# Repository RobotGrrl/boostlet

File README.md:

# Boostlet!

Embeddable circuit board to boost battery input to 5V intended for small robots. Useful access is provided to two logic level convertors for Neopixels, and a 3.3V regulator. Input and output are protected with PTCs, with the option to not populate with a solder jumper. Castellated connectors enable this circuit board to be added either surface mount or with through-hole 0.1" headers. 

---

## Documentation

[Boost IC: PAM2401](https://www.diodes.com/assets/Datasheets/PAM2401.pdf)

Dimensions: 35 mm x 40 mm

- V_IN: 0.9 - 4.75V
- V_OUT: 5V, 3A
- V_REG: 3.3V, 1A

### Connectors

J1
- VCC
- NEO_IN2
- NEO_OUT2
- BATT_SIG
- NEO_IN1
- NEO-OUT1
- GND

J2 (Input)
- V_IN (V_BATT)
- GND
- VCC

J3 (Output)
- V_OUT (5V)
- GND
- V_REG (3.3V)

### Solder Jumpers
- JP1: Bypass input PTC
- JP2: Enable 3.3V reg powered from 5V boost output
- JP3: Bypass output PTC
- JP4: Connect 3.3V reg output to Vcc _(be sure Vcc isn't connected to anything!)_

_Solder jumpers are open by default, add solder to connect the pads to close them_

Documentation provided under [CC-BY-4.0](https://creativecommons.org/licenses/by/4.0/)

---

## License

Boostlet! (C) Copyright Erin RobotZwrrl, Robot Missions Inc.

12-30-23 v1.0

[RobotZwrrl.xyz/boostlet](http://RobotZwrrl.xyz/boostlet)

[RobotMissions.org](https://RobotMissions.org)

This hardware is released under:

CERN Open Hardware License Version 2.0 - Permissive (CERN-OHL-P)

[https://cern-ohl.web.cern.ch/](https://cern-ohl.web.cern.ch/)

Disclaimer: Distributed as is. No warranty is given. Not responsible or liable for any damage or harm that result from this product.

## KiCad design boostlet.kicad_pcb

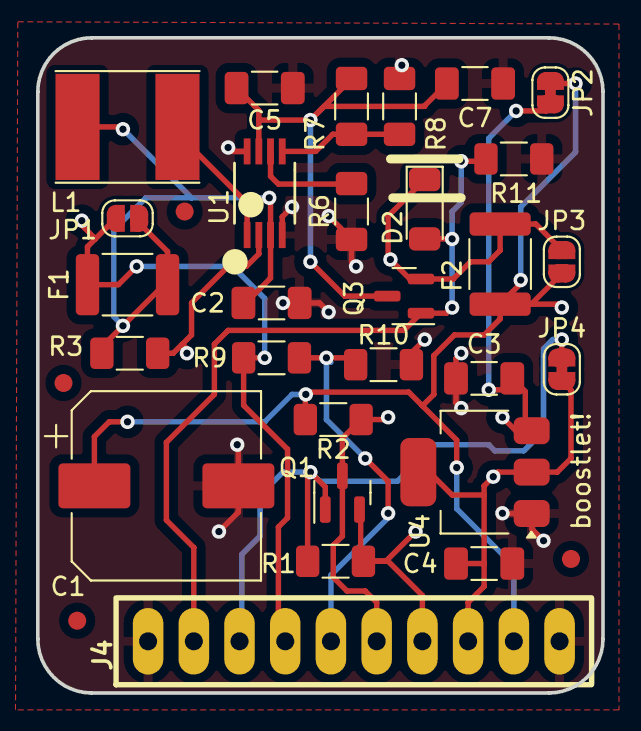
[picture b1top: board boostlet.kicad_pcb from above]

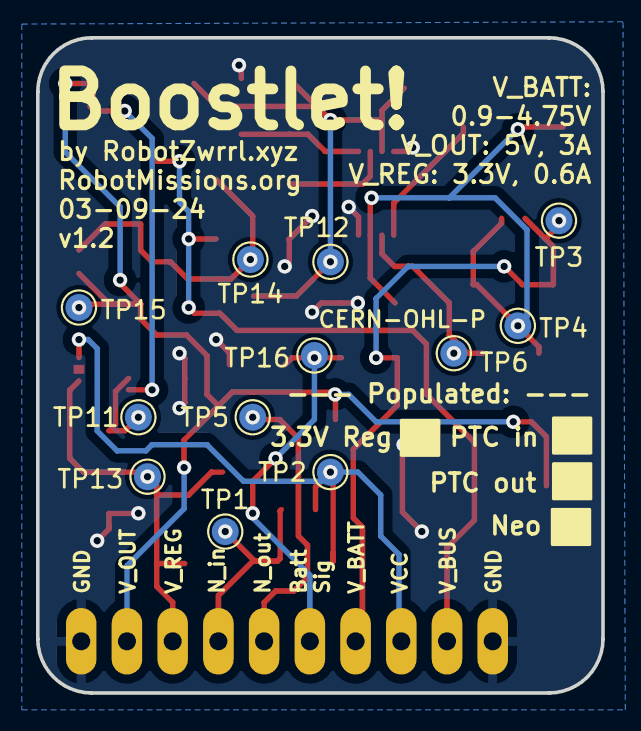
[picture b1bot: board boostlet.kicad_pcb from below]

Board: 2 copper layers, 31.4 x 36.4 mm, 44 parts (12 on the bottom side), 17 nets.

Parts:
C1: 1000 uF @ 16 V; CP_Elec_10x10
C2: 10 uF; C_1206_3216Metric_Pad1.33x1.80mm_HandSolder
C3, C4, C7: 1 uF; C_1206_3216Metric_Pad1.33x1.80mm_HandSolder
C5: 22 uF; C_1206_3216Metric_Pad1.33x1.80mm_HandSolder
D2: PMEG40T30ERX 40V 3A; D_SOD-123
F1: Polyfuse 6V, 1.5A I_h, 3A I_t, 500 ms; Fuse_1812_4532Metric_Pad1.30x3.40mm_HandSolder
F2: Polyfuse 16V, 1.25A I_h, 2.5A I_t, 400 ms; Fuse_1812_4532Metric_Pad1.30x3.40mm_HandSolder
FID1, FID2, FID3, FID4: Fiducial; Fiducial_1mm_Mask2mm
J4: Conn_01x10_Socket; Oval_1x10_P2.54mm
JP1, JP3: SolderJumper_2_Open; SolderJumper-2_P1.3mm_Open_RoundedPad1.0x1.5mm
JP2, JP4: SolderJumper_2_Bridged; SolderJumper-2_P1.3mm_Bridged_RoundedPad1.0x1.5mm
L1: 4.7 uH, 3 A; L_Taiyo-Yuden_NR-60xx_HandSoldering
Q1: BSS138; SOT-23
Q3: DMG3415U; SOT-23
R1, R2: 10k; R_1206_3216Metric_Pad1.30x1.75mm_HandSolder
R3, R6, R8, R11: 100k; R_1206_3216Metric_Pad1.30x1.75mm_HandSolder
R7: 750k; R_1206_3216Metric_Pad1.30x1.75mm_HandSolder
R9: 100; R_1206_3216Metric_Pad1.30x1.75mm_HandSolder
R10: 6.8k; R_1206_3216Metric_Pad1.30x1.75mm_HandSolder
TP1, TP2, TP3, TP4, TP5, TP6, TP11, TP12, TP13, TP14, TP15, TP16: TestPoint; TestPoint_Pad_D1.5mm
U1: PAM2401
U4: AP2111H-3.3TRG1; SOT-223-3_TabPin2

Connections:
/3.3V: C4.1, J4.8, JP4.1 (A), TP13.1, U4.2 (VO)
/5V: C1.1, F2.1, J4.9, JP2.1 (A), JP3.2 (B), R2.1, TP15.1
/BATT_SIG: J4.5, R9.2, R10.1, TP16.1
/NEO_IN1: J4.7, Q1.2 (S), R1.2, TP1.1
/NEO_OUT1: J4.6, Q1.3 (D), R2.2, TP5.1
/V_BATT: F1.2, J4.4, JP1.1 (A), R9.1, TP3.1
/V_BOOST: C5.1, C7.1, Q3.3 (D), R7.1, TP12.1, U1.7 (OUT)
/V_BUS: D2.2 (A), J4.2, Q3.1 (G), R11.1
GND: C1.2, C2.2, C3.2, C4.2, C5.2, C7.2, J4.1, J4.10, R6.2, R8.2, R10.2, R11.2, U1.4 (AGND), U1.8 (PGND), U4.1 (GND)
unnamed: D2.1 (K), F2.2, JP3.1 (A), Q3.2 (S), TP14.1
unnamed: C2.1, F1.1, JP1.2 (B), L1.1, R3.1, TP4.1, U1.3 (VIN)
unnamed: C3.1, JP2.2 (B), TP11.1, U4.3 (VI)
unnamed: R3.2, TP6.1, U1.2 (EN)
unnamed: R7.2, R8.1, U1.5 (FB)
unnamed: L1.2, U1.1 (LX)
unnamed: R6.1, U1.6 (RSET)
VCC: J4.3, JP4.2 (B), Q1.1 (G), R1.1, TP2.1

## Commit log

2023-12-31 Circuit board and schematic
2023-12-31 Info update
2024-03-09 Archive v1.0
2024-03-09 Version 1.2
2024-03-10 Information update
2024-03-16 Mysterious vault of boostletland
2024-03-16 Boostlet v1.2
2024-04-22 Mlep mlep rrrrr, zwap zwap zwap
